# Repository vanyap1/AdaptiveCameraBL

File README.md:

# AdaptiveCameraBL
Camera backlight module

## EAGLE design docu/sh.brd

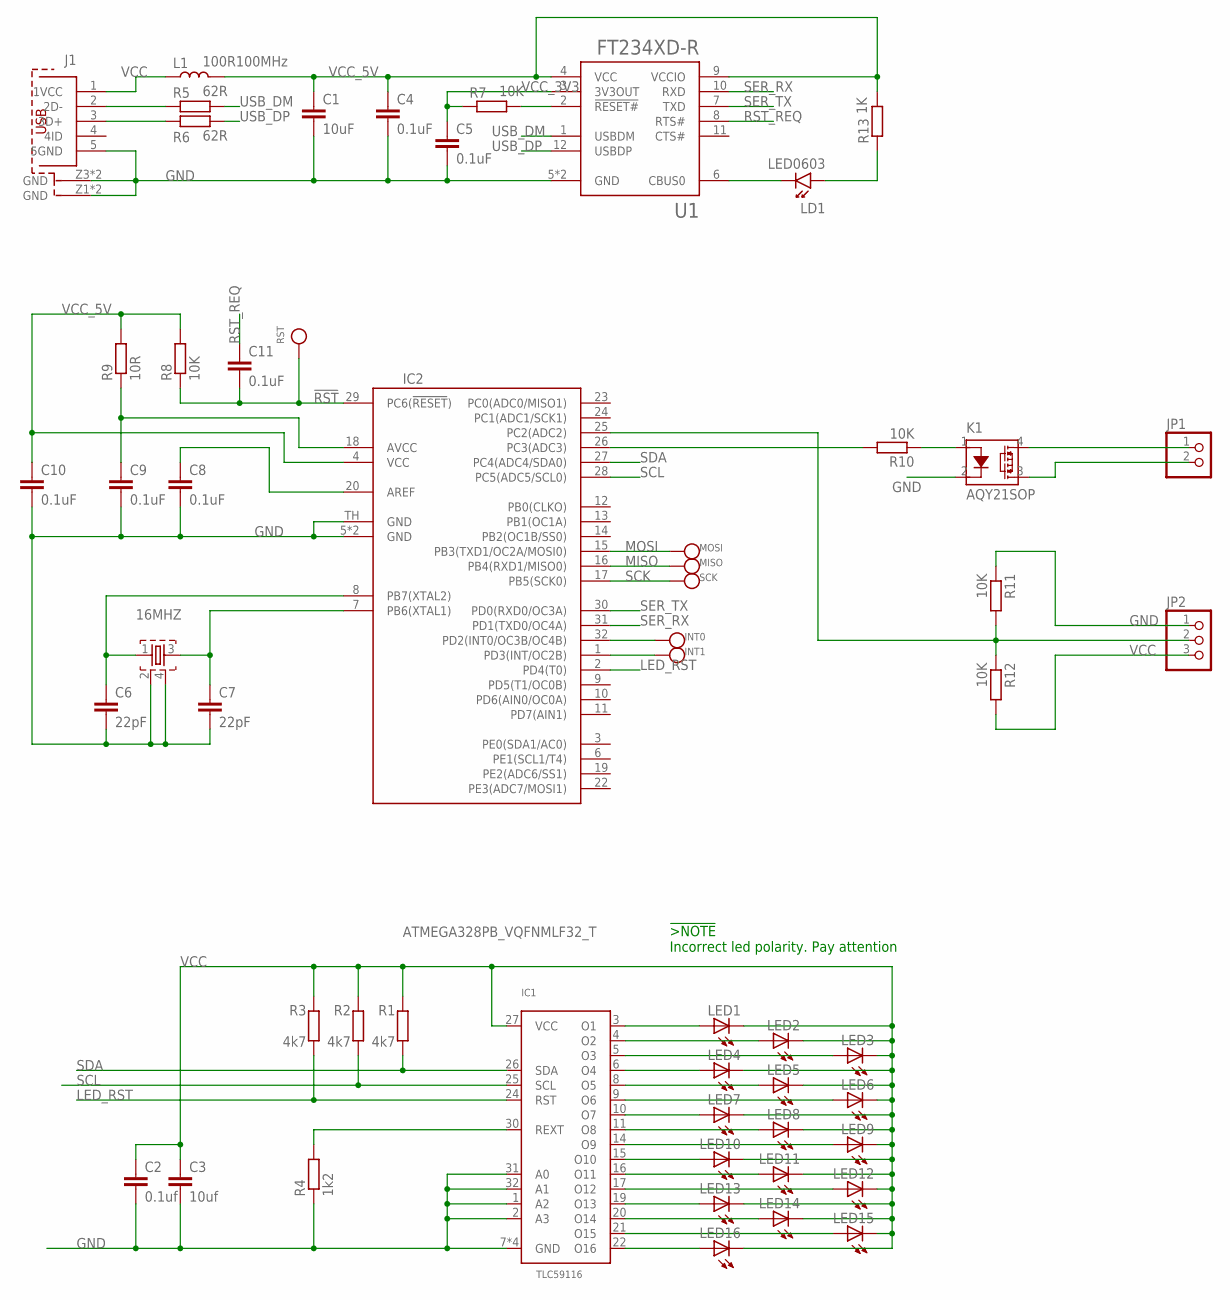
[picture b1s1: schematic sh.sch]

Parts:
16MHZ: QUARTZ_ZQ; QUARTZ_3X3MM
C1: 10uF; 1206
C2: 0.1uf; 0603
C3: 10uf; 1206
C4, C5, C8, C9, C10, C11: 0.1uF; 0603
C6, C7: 22pF; 0603
IC1: TLC59116; MLF32-TH
IC2: ATMEGA328PB_VQFNMLF32_T; MLF32-TH
INT0, INT1: TEST_POINT_D2MM; TP
J1: MINI_USB_TYP_B_@; 65100516121
JP1: PINHD-1X2LIGHT; 2X01
JP2: PINHD-1X3_LIGHT; 3X01
K1: AQY21SOP; SOP04
L1: 100R100MHz; 0805
LD1: LED0603; 0603_P
LED1, LED2, LED3, LED4, LED5, LED6, LED7, LED8, LED9, LED10, LED11, LED12, LED13, LED14, LED15, LED16: LED2KA-3528ASYC; KA-3528ASYC
MISO: TEST_POINT_D2MM; TP
MOSI: TEST_POINT_D2MM; TP
R1, R2, R3: 4k7; 0603
R4: 1k2; 0603
R5, R6: 62R; 0603
R7, R8, R10, R11, R12: 10K; 0603
R9: 10R; 0603
R13: 1K; 0603
RST: TEST_POINT_D2MM; TP
SCK: TEST_POINT_D2MM; TP
U1: FT234XD-R; IC_FT234XD-R

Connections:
!RST: C11.2, IC2.29 (PC6(!RESET!)), R8.1, RST.P$1
GND: 16MHZ.2, 16MHZ.4, C1.2, C2.2, C3.2, C4.2, C5.2, C6.2, C7.2, C8.2, C9.2, C10.2, IC1.1 (A2), IC1.2 (A3), IC1.7 (GND), IC1.18 (GND), IC1.23 (GND), IC1.31 (A0), IC1.32 (A1), IC1.TH (GND), IC2.5 (GND), IC2.21 (GND), IC2.TH (GND), J1.5 (5GND), J1.Z1 (GND), J1.Z2 (GND), J1.Z3 (GND), J1.Z4 (GND), JP2.1, K1.2 (K), R4.1, R11.1, U1.5 (GND), U1.13 (GND)
LED_RST: IC1.24 (RST), IC2.2 (PD4(T0)), R3.1
MISO: IC2.16 (PB4(RXD1/MISO0)), MISO.P$1
MOSI: IC2.15 (PB3(TXD1/OC2A/MOSI0)), MOSI.P$1
unnamed: IC1.3 (O1), LED1.A
unnamed: IC1.4 (O2), LED2.A
unnamed: IC1.5 (O3), LED3.A
unnamed: IC1.6 (O4), LED4.A
unnamed: IC1.8 (O5), LED5.A
unnamed: IC1.9 (O6), LED6.A
unnamed: IC1.10 (O7), LED7.A
unnamed: IC1.11 (O8), LED8.A
unnamed: IC1.14 (O9), LED9.A
unnamed: IC1.15 (O10), LED10.A
unnamed: IC1.16 (O11), LED11.A
unnamed: IC1.17 (O12), LED12.A
unnamed: IC1.19 (O13), LED13.A
unnamed: IC1.20 (O14), LED14.A
unnamed: IC1.21 (O15), LED15.A
unnamed: IC1.22 (O16), LED16.A
unnamed: IC2.26 (PC3(ADC3)), R10.2
unnamed: 16MHZ.1, C6.1, IC2.8 (PB7(XTAL2))
unnamed: J1.2 (2D-), R5.1
unnamed: IC2.32 (PD2(INT0/OC3B/OC4B)), INT0.P$1
unnamed: J1.3 (3D+), R6.1
unnamed: IC1.30 (REXT), R4.2
unnamed: 16MHZ.3, C7.1, IC2.7 (PB6(XTAL1))
unnamed: R7.2, U1.2 (!RESET#)
unnamed: C8.1, IC2.20 (AREF)
unnamed: C9.1, IC2.18 (AVCC), R9.1
unnamed: JP1.1, K1.4 (DS1)
unnamed: K1.1 (A), R10.1
unnamed: JP1.2, K1.3 (DS2)
unnamed: LD1.1 (K), U1.6 (CBUS0)
unnamed: LD1.2 (A), R13.1
unnamed: IC2.25 (PC2(ADC2)), JP2.2, R11.2, R12.1
unnamed: IC2.1 (PD3(INT/OC2B)), INT1.P$1
RST_REQ: C11.1, U1.8 (RTS#)
SCK: IC2.17 (PB5(SCK0)), SCK.P$1
SCL: IC1.25 (SCL), IC2.28 (PC5(ADC5/SCL0)), R2.1
SDA: IC1.26 (SDA), IC2.27 (PC4(ADC4/SDA0)), R1.1
SER_RX: IC2.31 (PD1(TXD0/OC4A)), U1.10 (RXD)
SER_TX: IC2.30 (PD0(RXD0/OC3A)), U1.7 (TXD)
USB_DM: R5.2, U1.1 (USBDM)
USB_DP: R6.2, U1.12 (USBDP)
VCC: C2.1, C3.1, IC1.27 (VCC), J1.1 (1VCC), JP2.3, L1.1, LED1.C, LED2.C, LED3.C, LED4.C, LED5.C, LED6.C, LED7.C, LED8.C, LED9.C, LED10.C, LED11.C, LED12.C, LED13.C, LED14.C, LED15.C, LED16.C, R1.2, R2.2, R3.2, R12.2
VCC_3V3: C5.1, R7.1, U1.3 (3V3OUT)
VCC_5V: C1.1, C4.1, C10.1, IC2.4 (VCC), L1.2, R8.2, R9.2, R13.2, U1.4 (VCC), U1.9 (VCCIO)

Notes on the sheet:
!>NOTE Incorrect led polarity. Pay attention

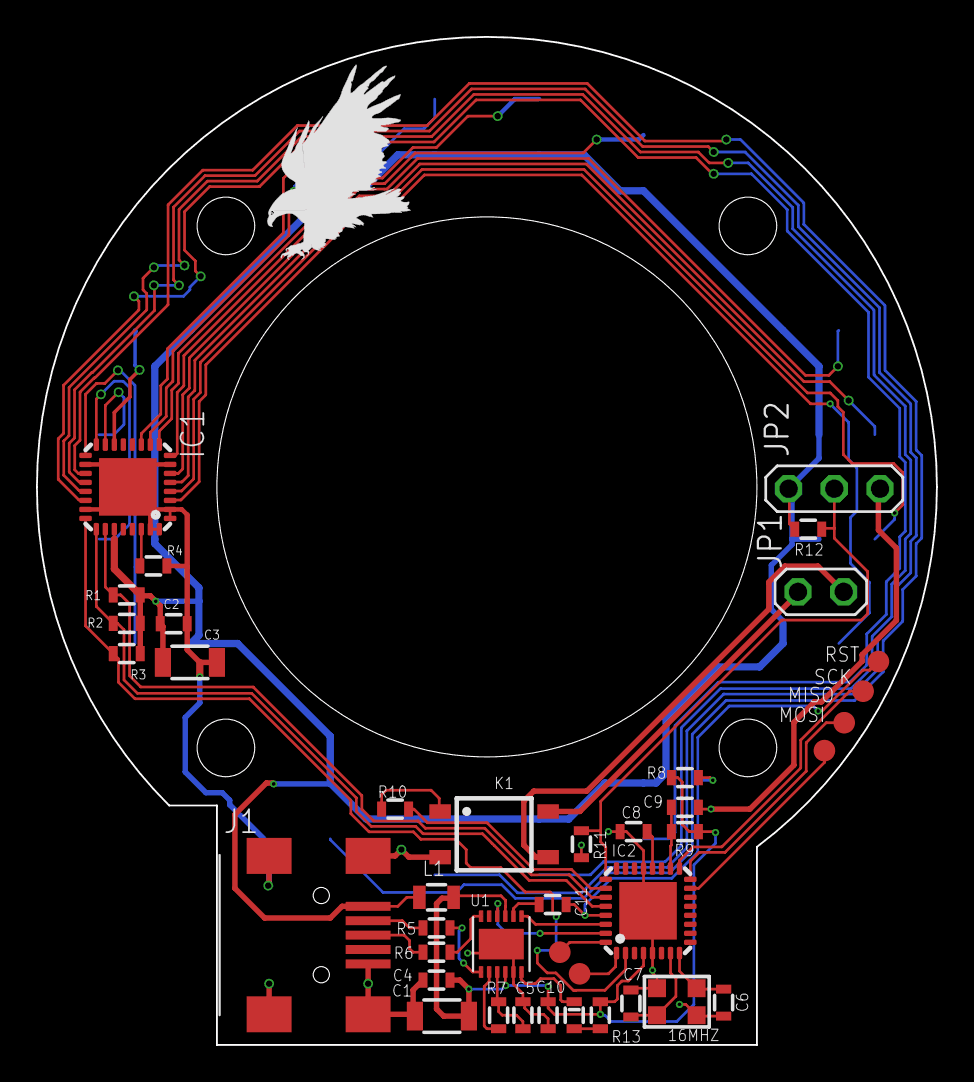
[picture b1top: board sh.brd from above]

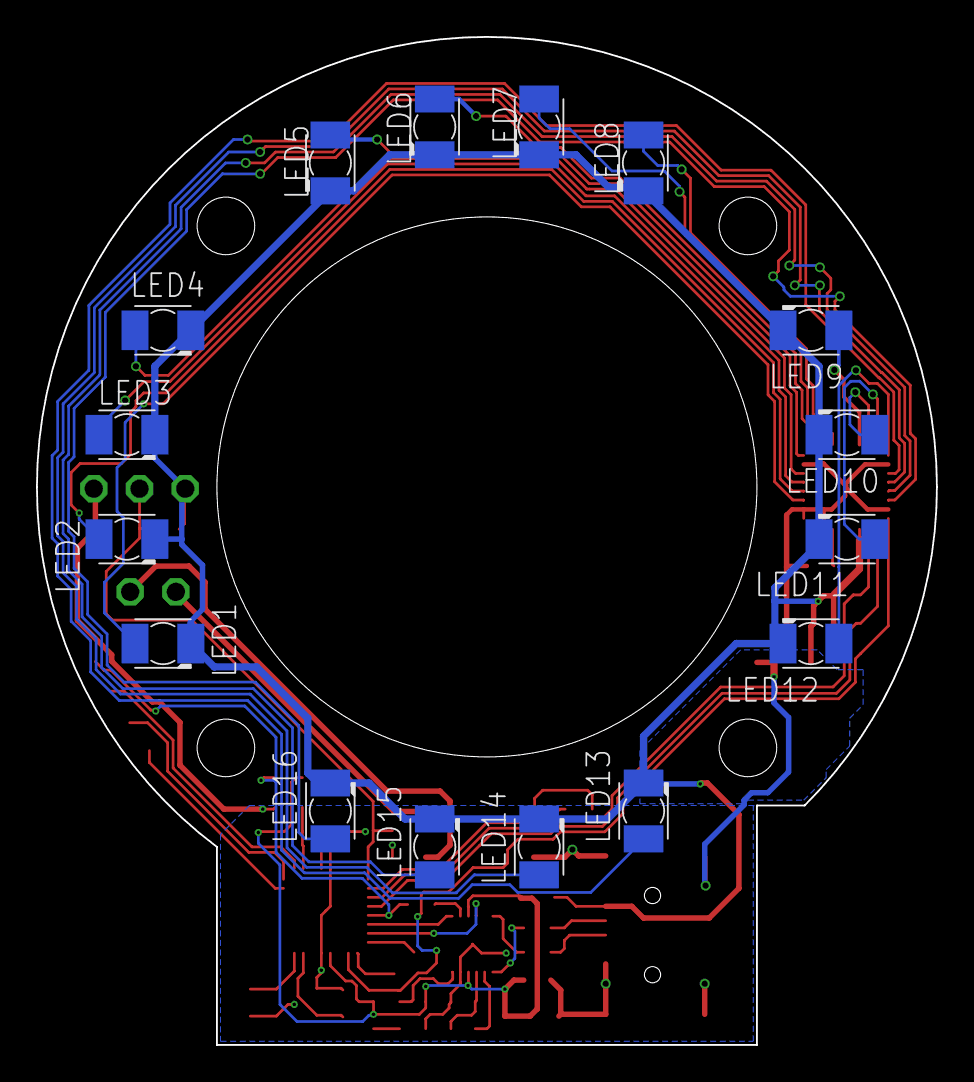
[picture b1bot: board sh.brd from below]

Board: 2 copper layers, 50.0 x 56.0 mm, 57 parts (16 on the bottom side), 49 nets.

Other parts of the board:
U$1: EAGLE-PLC-8MM

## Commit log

2024-04-19 Project upload
